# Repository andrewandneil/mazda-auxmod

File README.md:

# Mazda AuxMod

An effort to recreate the classic AuxMod for Mazda Radios from around 2000-2007 using code & PCB designs from NikoSapi's MazdaSpoof. 

Currently supports iPod controls from NikoSapi's design, and an Aux input. (CURRENTLY UNTESTED)

## Links

- The Original AuxMod: [sylfex.com](https://www.sylfex.com/products/AuxMod/)
- NikoSapi's MazdaSpoof: [nikosapi.org](https://nikosapi.org/w/index.php/MazdaSpoof_-_A_Tape_Deck_Emulator)

## Goals

- Produce something similar to the original AuxMod and NikoSapi's MazdaSpoof. 
- Design a simple connector (using 2 PCBs seperated by standoffs) to allow easy push-fit connection to the Radio with zero modification.

## TODO:

- [ ] Test circuit
- [ ] Design alternate way of connection for plugging into TAPE/MD port on radio
- [ ] Rewrite portions of code
- [ ] Native BlueTooth integration (skipping tracks etc)

## License

Uses code from NikoSapi, shared under GPLv3.

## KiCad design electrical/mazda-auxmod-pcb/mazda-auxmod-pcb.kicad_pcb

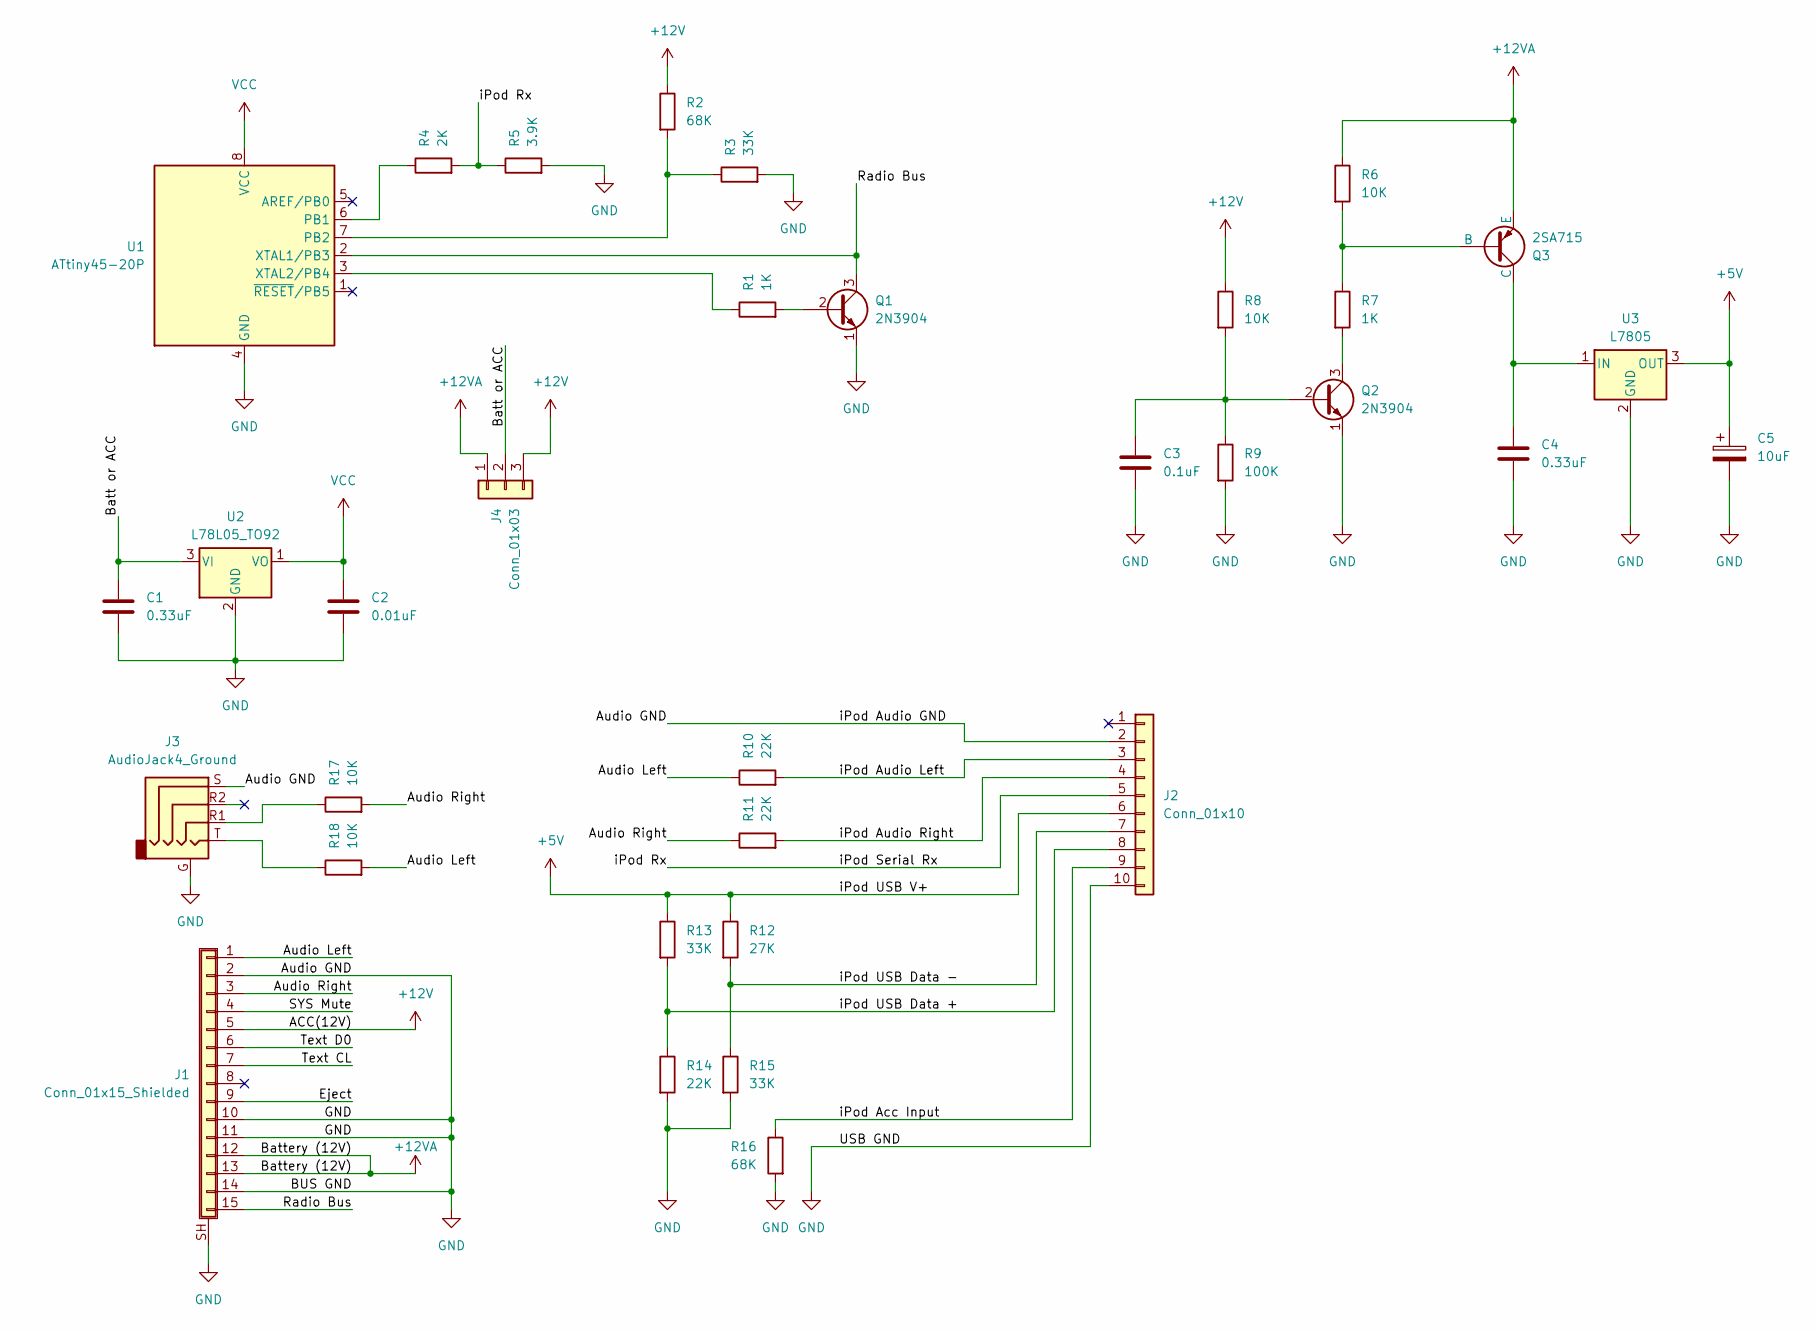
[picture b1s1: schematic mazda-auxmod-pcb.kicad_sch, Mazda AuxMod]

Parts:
C1, C4: 0.33uF; C_Disc_D5.0mm_W2.5mm_P2.50mm
C2: 0.01uF; C_Disc_D5.0mm_W2.5mm_P2.50mm
C3: 0.1uF; C_Disc_D5.0mm_W2.5mm_P2.50mm
C5: 10uF; CP_Radial_D5.0mm_P2.00mm
J1: Conn_01x15_Shielded; Mazda_Radio_Connector
J2: Conn_01x10; PinHeader_2x05_P2.54mm_Vertical
J3: AudioJack4_Ground; Jack_3.5mm_PJ320D_Horizontal
J4: Conn_01x03; SolderJumper-3_P1.3mm_Bridged2Bar12_RoundedPad1.0x1.5mm
Q1, Q2: 2N3904; TO-92_Inline
Q3: 2SA715; TO-126-3_Horizontal_TabDown
R1, R7: 1K; R_Axial_DIN0204_L3.6mm_D1.6mm_P7.62mm_Horizontal
R2, R16: 68K; R_Axial_DIN0204_L3.6mm_D1.6mm_P7.62mm_Horizontal
R3, R13, R15: 33K; R_Axial_DIN0204_L3.6mm_D1.6mm_P7.62mm_Horizontal
R4: 2K; R_Axial_DIN0204_L3.6mm_D1.6mm_P7.62mm_Horizontal
R5: 3.9K; R_Axial_DIN0204_L3.6mm_D1.6mm_P7.62mm_Horizontal
R6, R8, R17, R18: 10K; R_Axial_DIN0204_L3.6mm_D1.6mm_P7.62mm_Horizontal
R9: 100K; R_Axial_DIN0204_L3.6mm_D1.6mm_P7.62mm_Horizontal
R10, R11, R14: 22K; R_Axial_DIN0204_L3.6mm_D1.6mm_P7.62mm_Horizontal
R12: 27K; R_Axial_DIN0204_L3.6mm_D1.6mm_P7.62mm_Horizontal
U1: ATtiny45-20P; DIP-8_W7.62mm
U2: L78L05_TO92; TO-92_Inline
U3: L7805; TO-220-3_Horizontal_TabDown

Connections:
+5V: C5.1, J2.6, R12.1, R13.1, U3.3 (OUT)
+12V: J1.5, J4.3, R2.1, R8.1
+12VA: J1.12, J1.13, J4.1, Q3.3 (E), R6.1
/Audio Left: J1.1, R10.1, R18.2
/Audio Right: J1.3, R11.1, R17.2
/Batt or ACC: C1.1, J4.2, U2.3 (VI)
/Eject: J1.9
/Radio Bus: J1.15, Q1.3 (C), U1.2 (XTAL1/PB3)
/SYS Mute: J1.4
/Text CL: J1.7
/Text D0: J1.6
/iPod Acc Input: J2.9, R16.1
/iPod Audio Left: J2.3, R10.2
/iPod Audio Right: J2.4, R11.2
/iPod Rx: J2.5, R4.2, R5.1
/iPod USB Data +: J2.8, R13.2, R14.1
/iPod USB Data -: J2.7, R12.2, R15.1
GND: C1.2, C2.2, C3.2, C4.2, C5.2, J1.2, J1.10, J1.11, J1.14, J1.SH (Shield), J2.2, J2.10, J3.G, J3.S, Q1.1 (E), Q2.1 (E), R3.2, R5.2, R9.2, R14.2, R15.2, R16.2, U1.4 (GND), U2.2 (GND), U3.2 (GND)
unnamed: J3.R1, R17.1
unnamed: J3.T, R18.1
unnamed: Q1.2 (B), R1.2
unnamed: C3.1, Q2.2 (B), R8.2, R9.1
unnamed: Q2.3 (C), R7.2
unnamed: Q3.2 (B), R6.2, R7.1
unnamed: C4.1, Q3.1 (C), U3.1 (IN)
unnamed: R4.1, U1.6 (PB1)
unnamed: R2.2, R3.1, U1.7 (PB2)
unnamed: R1.1, U1.3 (XTAL2/PB4)
VCC: C2.1, U1.8 (VCC), U2.1 (VO)

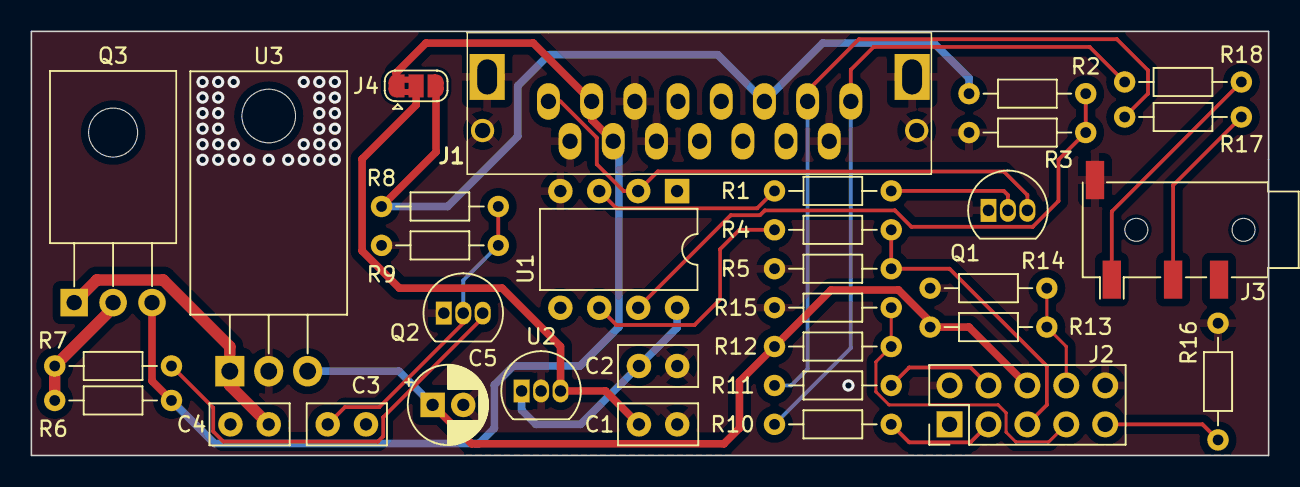
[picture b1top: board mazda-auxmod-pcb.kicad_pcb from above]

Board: 2 copper layers, 80.8 x 27.7 mm, 33 parts (0 on the bottom side), 25 nets.

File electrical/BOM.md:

# Bill of Materials for Mazda AuxMod (Rev 1.0)

## Universal (AUX jack or iPod):
- R1 - 1K
- R17 - 10K
- R18 - 10K

- C1 - 0.33uF
- C2 - 0.01uF

- U1 - ATtiny45
- U2 - 78L05

- Q1 - 2n3904

- J1 - Mazda Radio Connector


## In Addition:

### Only Aux In:
- J3 - PJ-320D

### Only iPod Integration:
- R2 - 68K
- R3 - 33K
- R4 - 2K
- R5 - 3.9K
- R6 - 10K
- R7 - 1K
- R8 - 10K
- R9 - 100K
- R10 - 22K
- R11 - 22K
- R12 - 27K
- R13 - 33K
- R14 - 22K
- R15 - 33K
- R16 - 68K

- C3 - 0.1uF
- C4 - 0.33uF
- C5 - 10uF

- U3 - L7805

- Q2 - 2n3904
- Q3 - 2sa715 or 2sb744

- J2 - 2x5 2.54mm Pin Header

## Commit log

2024-04-06 inital file structure
2024-04-06 PCB Rev 1.0
2024-04-06 updated gitignore
2024-04-06 Deleted .DS_STORE
2024-04-06 Removed .DS_Store
2024-04-06 fixed links in README
2024-04-06 fixed README formatting
2024-04-07 Added Schematic PDF
2024-04-07 added BOM text file placeholder
2024-04-07 added TODO to README
2024-04-07 neatened up schematic/pcb
2024-04-07 added README to firmware folder
2024-04-07 added gerber files for rev 1.0
2024-04-07 changed BOM from txt to md
2024-04-07 updated BOM, changed formatting
2024-04-08 fixed footprint for radio connector
2024-04-08 Create LICENSE
2024-04-08 added version info to pcb
